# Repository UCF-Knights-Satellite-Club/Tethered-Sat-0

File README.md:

# Tethered-Sat-0
Tethered-Sat-0 or T-Sat-0 is Knights Satellite Club's first CubeSat mission. This a suborbital, tethered balloon mission.

## Hardware
This mission uses one PCB which has been designed in Autodesk EAGLE. The PCB holds several breakout boards, connectors, and an ESP32 devkit for ease of design and testing. The PCB fits into a 1U frame along with an Arducam Mega, a battery, and a parachute deployment system. The burn-wire system consists of two RFM radio modules, one flies with the CubeSat and recieves the signal from the ground station which sends the burn command. Once the burn command is recieved, a Seeduino XIAO will activate a transistor connected to a nichrome wire which melts through a monofilament fishing line and drops T-Sat-0.

## Software
This project utilizes the Arduino ecosystem on a **DOIT ESP32 DEVKIT V1** and two **Seeeduino XIAO**s. Unless stated otherwise, all libraries can be found in the Arduino IDE Library Manager.

### Prerequisites
- **Arduino ESP32 Core** ([installation instructions](https://docs.espressif.com/projects/arduino-esp32/en/latest/installing.html))
- **Seeeduino Arduino IDE Support** ([installation instructions](https://wiki.seeedstudio.com/Seeed_Arduino_Boards/))
- **Radiohead** by Mike McCauley (Arduino IDE Library Manager version is old, [download directly](http://www.airspayce.com/mikem/arduino/RadioHead/))
- **Adafruit MMA8451 Library** by Adafruit
- **Adafruit BMP3XX Library** by Adafruit
- **Adafruit GFX Library** by Adafruit
- **Adafruit SSD1306** by Adafruit
- **Arducam_Mega** by Arducam
- **ESP32Servo** by Kevin Harrington

### Explanation
The flight software has five states. The first state is `CALIBRATION` which averages several altitude readings to determine a launch altitude. Next is `PREFLIGHT` which runs when T-Sat-0 is on the ground and waiting to be released on the balloon. High acceleration or breaking an altitude threshold will move to the `ASCENT` state. In this state, T-Sat-0 monitors acceleration to determine when it is in free fall. In free fall, the accelerometer will read close to zero. Once this condition is met, the state moves to `FREEFALL` where altitude is compared to the deployment altitude. Once deployment altitude is reached, the parachute is deployed and the state switches to `LANDING`.

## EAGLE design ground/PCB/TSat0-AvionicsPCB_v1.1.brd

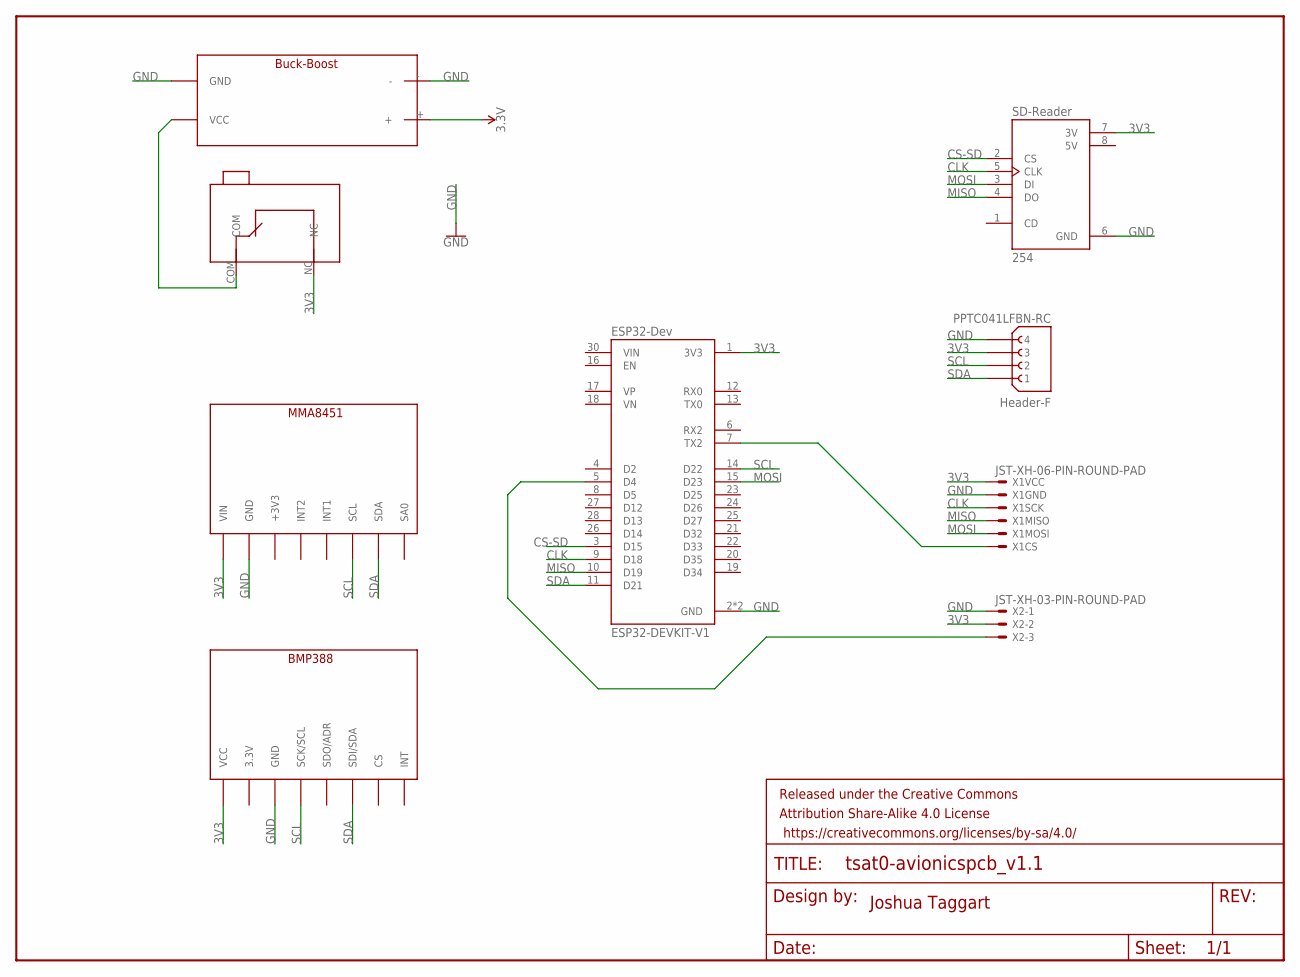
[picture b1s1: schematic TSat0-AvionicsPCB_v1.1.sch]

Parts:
BMP388: BMP388; BMP388-FP
FRAME1: FRAME-LETTERNO_PACKAGE; DUMMY
J1: PPTC041LFBN-RC; SULLINS_PPTC041LFBN-RC
MMA8451: MMA8451; MMA8451-FP
U1: ESP32-DEVKIT-V1; MODULE_ESP32_DEVKIT_V1
U2: 254; MODULE_254
U$1: BUCKBOOST-LIPO; BUCKBOOST-FP
U$2: OMRON-MICROSWITCH; OMRON-MICROSWITCH-FP
X1: JST-XH-06-PIN-ROUND-PAD; JST-XH-06-PACKAGE-ROUND-PAD
X2: JST-XH-03-PIN-ROUND-PAD; JST-XH-03-PACKAGE-ROUND-PAD

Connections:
3.3V: U$1.+
3V3: BMP388.VCC, J1.3, MMA8451.VIN, U1.1 (3V3), U2.7 (3V), U$2.NC, X1.VCC, X2.2
5V: U2.8 (5V)
CLK: U1.9 (D18), U2.5 (CLK), X1.SCK
CS-SD: U1.3 (D15), U2.2 (CS)
GND: BMP388.GND, J1.4, MMA8451.GND, U1.2 (GND), U1.29 (GND), U2.6 (GND), U$1.-, U$1.GND, X1.GND, X2.1
MISO: U1.10 (D19), U2.4 (DO), X1.MISO
MOSI: U1.15 (D23), U2.3 (DI), X1.MOSI
unnamed: U1.7 (TX2), X1.CS
unnamed: U$1.VCC, U$2.COM
unnamed: U1.5 (D4), X2.3
SCL: BMP388.SCK/SCL, J1.2, MMA8451.SCL, U1.14 (D22)
SDA: BMP388.SDI/SDA, J1.1, MMA8451.SDA, U1.11 (D21)

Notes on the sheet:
Joshua Taggart

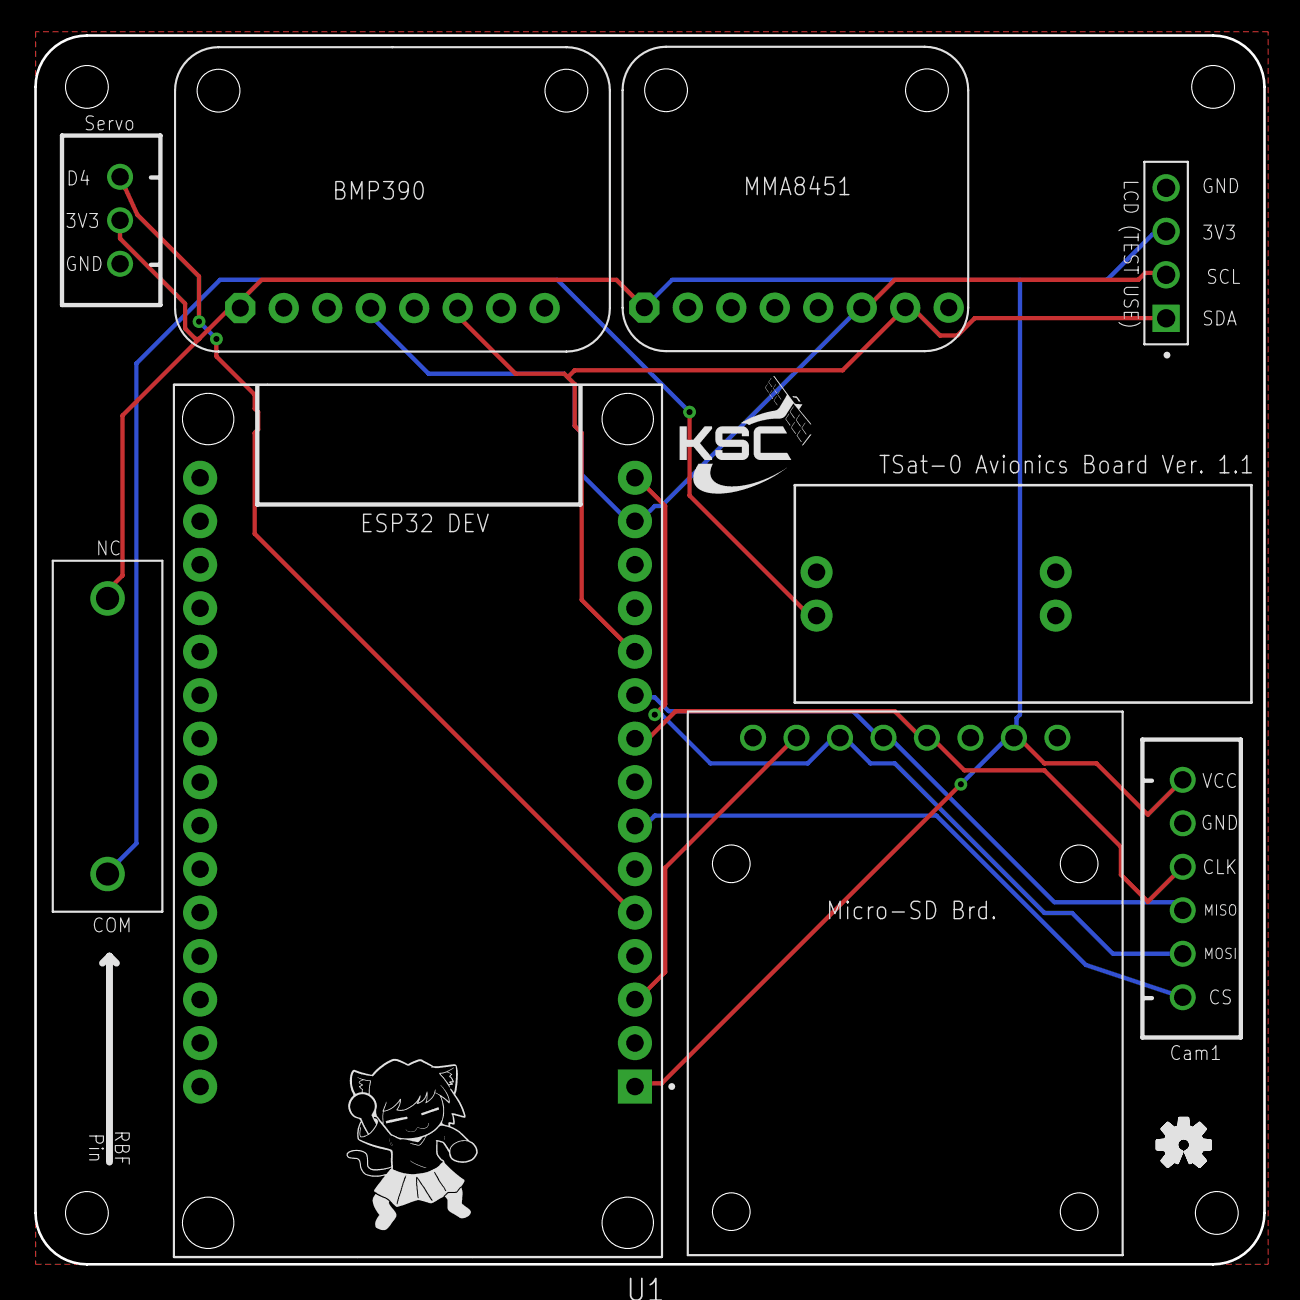
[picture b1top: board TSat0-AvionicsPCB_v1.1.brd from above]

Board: 2 copper layers, 71.8 x 71.8 mm, 11 parts (0 on the bottom side), 11 nets.

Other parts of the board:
U$3: OSHW-LOGO-S

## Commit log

2024-03-02 added folders, camera test code
2024-03-27 changed file layout, lora test codes, pcb design filles
2024-06-16 fsw for testing work
2024-09-27 Added testing for the timer interrupt
2024-11-01 Added task for checking altitude
2024-11-18 altitude triggered deployment
2024-11-18 time based deployment test
2024-11-18 reorganize repo
2024-11-18 remove old files
2024-11-18 burnwire radio code
2024-11-18 removed unnecessary functions, fixed compiling
2024-11-18 led indicate software reset
2024-11-18 clean up redundant code
2024-11-19 Improved code readability
2024-11-19 More code readability improvements.
2024-11-19 Ready for SD Card Testing, added log function
2024-11-20 Create burnwire_recv2
    Update burnwire recv radio with the button
2024-11-20 Rename burnwire_recv2 to software/burnwire_recv2
2024-11-20 Rename software/burnwire_recv2 to software/burnwire_recv/burnwire_recv2
2024-11-20 burnwire_send
    updated code
2024-11-20 include .vscode in gitignore, move to root
2024-11-20 replace old burnwire code
2024-11-20 demo for mma8451 module
2024-11-21 change freefall detection to use accelerometer
2024-11-21 reverse linkage direction
2024-11-22 move back to task based checking and add logging
2024-11-22 data storage changes
2024-11-22 added calculate altitude function
2024-11-22 deleted readAltitude so we call performReading ourselves
2024-11-22 read absolute altitude to data storage
2024-12-04 bring back camera code
2024-12-05 faster image saving, still having corruption issues
2024-12-05 wrap all spi access in mutex
2024-12-06 queue telemetry logs to avoid fighting over mutex
2024-12-06 add comments and fix spacing
2024-12-06 remove consistent value check
2025-01-16 filter accel components seperately
2025-01-16 run altitude checks even if sd mount fails
2025-01-16 remove F() macros, not needed on esp32
2025-01-16 detect freefall using bmp
2025-01-17 Update burnwire_recv.ino
    testing changes
2025-01-18 enable radio on boot
2025-01-18 fix trigger pin
2025-01-18 fix recv and send mixup
2025-01-18 cleanup
2025-01-18 sleep radio during burn
2025-01-20 Update burnwire_recv.ino
    burnwire_recv changes
2025-01-20 better testing values
2025-01-20 flight config
2025-06-09 fix i2c errors and image corruption
2025-06-11 major image speedup and corruption fix
2025-06-11 remove accelerometer mode change
2025-06-25 Flight Values

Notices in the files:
parts and their libraries:
SparkFun-Aesthetics: Licensing: Creative Commons ShareAlike 4.0 International - https://creativecommons.org/licenses/by-sa/4.0
SparkFun-Aesthetics: Released under the Creative Commons Attribution Share-Alike 4.0 License
SparkFun-Aesthetics: https://creativecommons.org/licenses/by-sa/4.0
